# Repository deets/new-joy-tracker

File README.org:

* New Joy Sensor Board

This is documentation for the sensor board I'm developing.

** Sensor Cable Color Coding

I use a 5-wire cable to support the external pressure sensors.

The following table lists the assignment of functions to color:

|--------+----------+---------+--------------|
| Color  | Function | DIN Pin | Sensor Board |
|--------+----------+---------+--------------|
| Black  | GND      |       1 |            1 |
| Brown  | 5V       |       5 |            5 |
| Grey   | 3.3V     |       X |            X |
| Yellow | SDA      |       4 |            4 |
| Blue   | SCL      |       3 |            3 |
|--------+----------+---------+--------------|

** Price Calculation

All calculations are based on a total of 20 Boards.

| Component       | Price per unit |
|-----------------+----------------|
| PCB             |           9.00 |
| ESP32           |          10.00 |
| DC/DC Converter |           4.00 |
|                 |                |

** PCB 

  - https://portal.multi-circuit-boards.eu/
  - [[https://www.amazon.de/gp/product/B0178DX1ZC/ref%3Doh_aui_search_detailpage?ie%3DUTF8&psc%3D1][DC/DC converter]]
  - [[https://www.reichelt.de/OeLFLEX-CLASSIC/CL100-5G0-5-50/3/index.html?ACTION%3D3&LA%3D3&ARTICLE%3D165213&GROUPID%3D7698&trstct%3Dvrt_pdn][5 wire cable]]
  - [[https://e2e.ti.com/support/interface/i2c/f/390/t/615703?P82B715-Not-reading#][P82B715 setup example]]
  - [[http://www.mathertel.de/Arduino/DMXShield.aspx][Good explanation of DMX transmitter setup]]
  - [[https://www.youtube.com/watch?v%3D8NDq6hC9KJo][ESP32 power consumption assessment]]
  - [[https://github.com/clacktronics/pyb_dmx/blob/master/dmx.py][Crappy but useful uPy implementation of DMX]]
  - [[https://de.wikipedia.org/wiki/DMX_(Lichttechnik)][DMX connector assignment]]
  - [[https://www.element14.com/community/groups/open-source-hardware/blog/2017/08/24/dmx-explained-dmx512-and-rs-485-protocol-detail-for-lighting-applications][Nice DMX512 intro]]
  - [[https://www.reichelt.de/PT15-Pihertrimmer-15mm/PT-15-L-10K/3/index.html?ACTION%3D3&LA%3D446&ARTICLE%3D14951&GROUPID%3D3128&artnr%3DPT%2B15-L%2B10K&SEARCH%3Dtrim%252Bpoti%252B10K&trstct%3Dpos_0][Trimm-Poti 10K]]
  - [[https://www.reichelt.de/Elkos-SMD-Low-ESR-105-C/SMD-ELKO-10-35/3/index.html?ACTION%3D3&LA%3D446&ARTICLE%3D31907&GROUPID%3D4001&artnr%3DSMD%2BELKO%2B10%252F35&SEARCH%3Dsmd%252Belko&trstct%3Dpos_1][SMD Elko]]

*** Pull up calculation

According to the P82B715 datasheet we need to calculate the pullups for the buffered bus as follows:

#+BEGIN_QUOTE
R = 1 μs/(C_device + C_wiring)

where

 - C_device = Sum of any connected device capacitances
 - C_wiring = Total wiring and stray capacitance on the bus section 

If these capacitances cannot be measured or calculated, an
approximation can be made by assuming that each device presents 10 pF
of load capacitance and 10 pF of trace capacitance, and that cables
range from 50 pF to 100 pF per meter.
#+END_QUOTE
 
For our use-case with up to 4 devices connected, the calculation should be

4 devices connected with a meter cable each:

20pF * 4 + (100pF * 4) = 500pF -> 0.000001 / (0.000000000500) = 2KOhm

** ESP32

*** Physical

*** Useful links

 - [[http://esp32.net/#Hardware][Overview of boards from espressif themselves]]
 - [[http://playground.arduino.cc/Main/MPU-6050][MPU6050 programming with the Arduino]]
 - [[https://github.com/kriswiner/ESP32/blob/master/MPU9250_MS5637/MPU9250_MS5637_AHRS.ino][ESP32 IMU Sensor Fusion Project]]
 - [[https://www.adafruit.com/product/439][I2C Light (visible/IR) Sensor ]]
 - [[https://github.com/nkolban/esp32-snippets][ESP32 native SDK snippets]]

*** References

bme280 code pilfered from

  https://github.com/catdog2/mpy_bme280_esp8266

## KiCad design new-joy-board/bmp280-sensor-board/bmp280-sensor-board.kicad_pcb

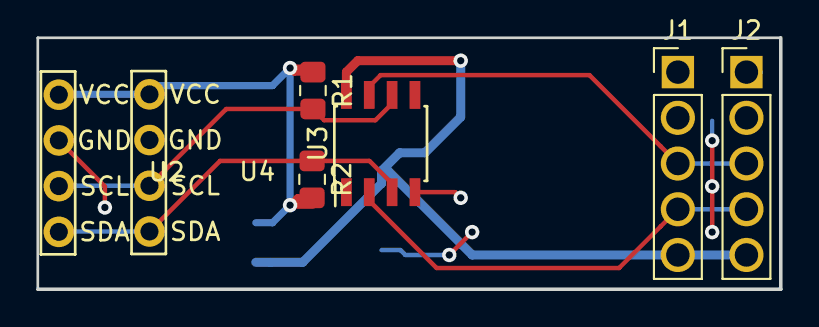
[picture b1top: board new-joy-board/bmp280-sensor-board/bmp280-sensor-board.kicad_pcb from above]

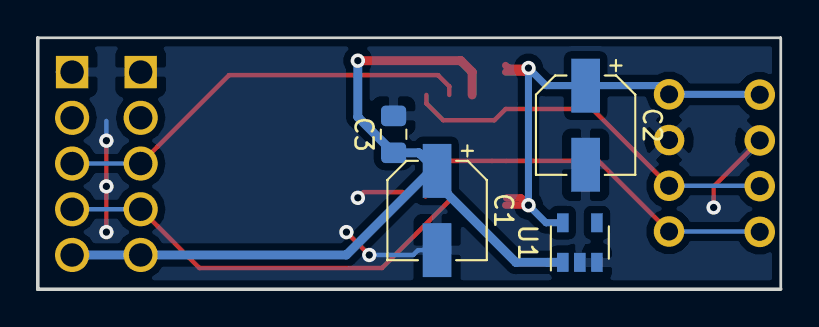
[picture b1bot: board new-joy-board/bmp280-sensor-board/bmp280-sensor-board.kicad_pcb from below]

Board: 2 copper layers, 41.3 x 14.0 mm, 11 parts (4 on the bottom side), 7 nets.

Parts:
C1, C2: 47uF; CP_Elec_5x5.8
C3: 0.1uF; C_0805_2012Metric_Pad1.15x1.40mm_HandSolder
J1, J2: Conn_01x05; Buffered-I2C-Cable-Connector
R1, R2: 2K2; R_0805_2012Metric_Pad1.15x1.40mm_HandSolder
U1: TPS76933; SOT-23-5
U2, U4: generic-i2c-device
U3: P82B715; P82B715D

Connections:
+3V3: C2.1, R1.1, R2.2, U1.5, U2.1, U4.1
+5V: C1.1, C3.1, J1.5, J2.5, U1.1, U3.8
/SCL: R1.2, U2.3, U3.6, U4.3
/SCLBUF: J1.3, J2.3, U3.7
/SDA: R2.1, U2.4, U3.3, U4.4
/SDABUF: J1.4, J2.4, U3.2
GND: C1.2, C2.2, C3.2, J1.1, J2.1, U1.2, U1.3, U2.2, U3.4, U4.2

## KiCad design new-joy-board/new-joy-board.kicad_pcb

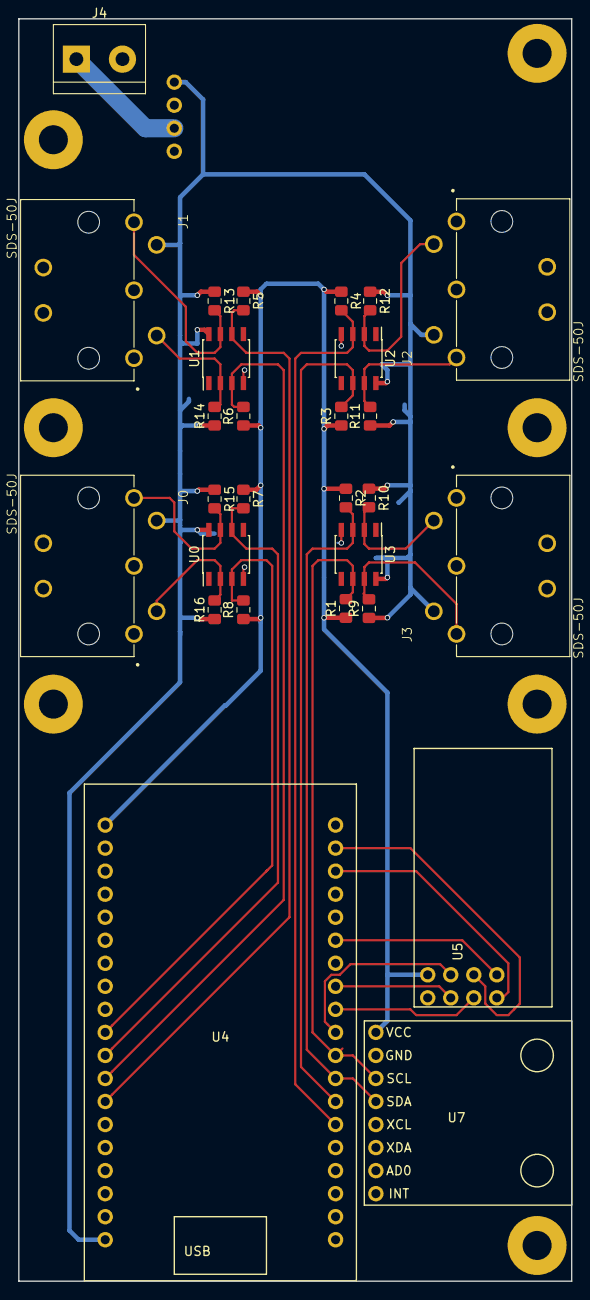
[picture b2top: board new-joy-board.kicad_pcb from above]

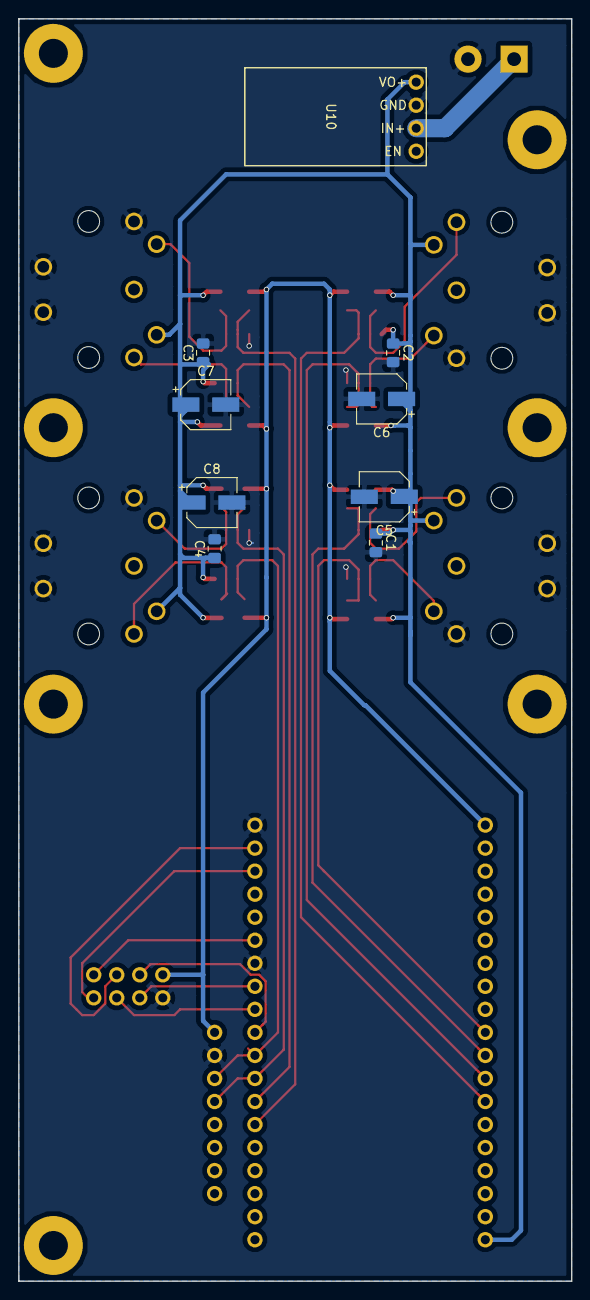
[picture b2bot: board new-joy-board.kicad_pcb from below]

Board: 2 copper layers, 61.0 x 139.2 mm, 37 parts (9 on the bottom side), 26 nets.

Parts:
C1, C2, C3, C4: 0.1uF; C_0805_2012Metric_Pad1.15x1.40mm_HandSolder
C5, C6, C7, C8: 47uF; CP_Elec_5x5.8
J0, J1, J2, J3: SDS-50J; CUI_SDS-50J
J4: BAT; TerminalBlock_bornier-2_P5.08mm
R1, R2, R3, R4, R5, R6, R7, R8, R9, R10, R11, R12, R13, R14, R15, R16: 2K2; R_0805_2012Metric_Pad1.15x1.40mm_HandSolder
U0, U1, U2, U3: P82B715; P82B715D
U4: AZReady_ESP32
U5: 24L01
U7: MPU6050_Breakout
U10: oskj-dc-dc

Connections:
+3V3: R1.1, R2.1, R3.1, R4.1, R5.1, R6.1, R7.1, R8.1, U4.1, U5.8, U7.1
+5V: C1.1, C2.1, C3.1, C4.1, C5.1, C6.1, C7.1, C8.1, J0.5, J1.5, J2.5, J3.5, R9.1, R10.1, R11.1, R12.1, R13.1, R14.1, R15.1, R16.1, U0.8, U1.8, U2.8, U3.8, U4.19, U10.1
+BATT: J4.1, U10.3
-BATT: C1.2, C2.2, C3.2, C4.2, C5.2, C6.2, C7.2, C8.2, J0.1, J0.S1, J0.S2, J1.1, J1.S1, J1.S2, J2.1, J2.S1, J2.S2, J3.1, J3.S1, J3.S2, J4.2, U0.4, U1.4, U2.4, U3.4, U4.32, U4.38, U5.4, U7.2, U10.2
/CE: U4.31, U5.3
/CLK: U4.30, U5.2
/CS0: U4.29, U5.7
/IRQ: U4.33, U5.5
/MISO: U4.36, U5.1
/MOSI: U4.37, U5.6
/SCL0BUF: J0.3, R15.2, U0.7
/SCL0ESP: R7.2, U0.6, U4.11
/SCL1BUF: J1.3, R13.2, U1.7
/SCL1ESP: R5.2, U1.6, U4.13
/SCL2BUF: J2.3, R11.2, U2.7
/SCL2ESP: R3.2, U2.6, U4.26
/SCL3BUF: J3.3, R9.2, U3.7
/SCL3ESP: R1.2, U3.6, U4.28, U7.3
/SDA0BUF: J0.4, R16.2, U0.2
/SDA0ESP: R8.2, U0.3, U4.10
/SDA1BUF: J1.4, R14.2, U1.2
/SDA1ESP: R6.2, U1.3, U4.12
/SDA2BUF: J2.4, R12.2, U2.2
/SDA2ESP: R4.2, U2.3, U4.25
/SDA3BUF: J3.4, R10.2, U3.2
/SDA3ESP: R2.2, U3.3, U4.27, U7.4

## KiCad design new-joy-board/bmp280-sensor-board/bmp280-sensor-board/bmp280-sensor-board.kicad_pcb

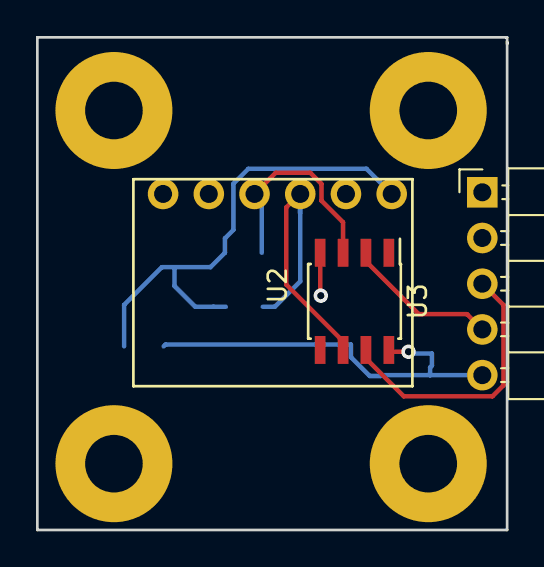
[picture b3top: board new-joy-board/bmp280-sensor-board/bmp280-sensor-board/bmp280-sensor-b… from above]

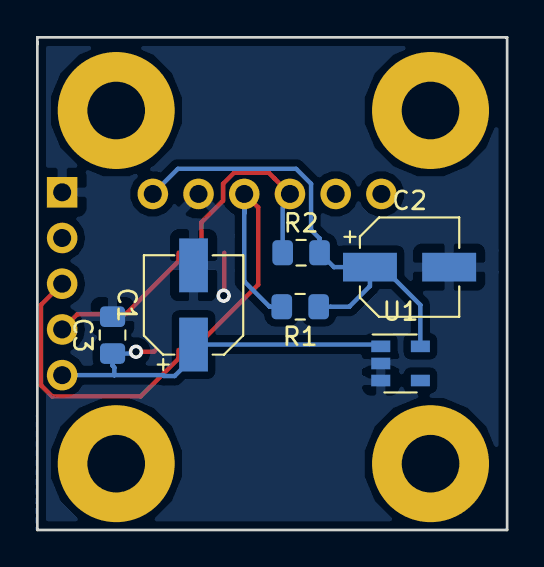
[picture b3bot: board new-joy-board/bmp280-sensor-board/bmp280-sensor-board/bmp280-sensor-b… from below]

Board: 2 copper layers, 26.1 x 27.4 mm, 9 parts (6 on the bottom side), 7 nets.

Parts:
C1, C2: 47uF; CP_Elec_5x5.8
C3: 0.1uF; C_0805_2012Metric_Pad1.15x1.40mm_HandSolder
J1: Conn_01x05; PinHeader_1x05_P2.54mm_Horizontal
R1, R2: 2K2; R_0805_2012Metric_Pad1.15x1.40mm_HandSolder
U1: TPS76933; SOT-23-5
U2: bmp280-board; bmp280-board-footprint
U3: P82B715; P82B715D

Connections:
+3V3: C2.1, R1.1, R2.2, U1.5, U2.1
+5V: C1.1, C3.1, J1.5, U1.1, U3.8
/SCL: R1.2, U2.3, U3.6
/SCLBUF: J1.3, U3.7
/SDA: R2.1, U2.4, U3.3
/SDABUF: J1.4, U3.2
GND: C1.2, C2.2, C3.2, J1.1, U1.2, U1.3, U2.2, U3.4

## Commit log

2018-06-08 First commit, simple setup and readout of bmp280 works
2018-06-15 Begin work on ESP and other component library
2018-06-15 First iteration footprint
2018-06-15 part update
2018-06-15 Began price calculation
2018-06-16 First stab at dc_dc_converter
2018-06-16 silk screen outline
2018-06-16 Associate footprints and adjust pads for library
2018-06-16 3V3 power regulator and i2c0 bus
2018-06-16 Add MPU6050 breakout board schematic and footprint
2018-06-16 Update documentation
2018-06-17 Add Datasheets
2018-06-17 Add P82B715 I2C extender to library
2018-06-17 Updated datasheet
2018-06-17 Add concrete component links and I2C bus impedance calculation
2018-06-17 Worked on design, including DMX and buffered I2C
2018-06-22 Implemented first stab of network setup and broadcasting
2018-06-24 Integrate MPU6050 from https://github.com/larsks/py-mpu6050
2018-06-29 Start working on actual message protocol
2018-06-29 Enhance protocol with timestamp and sequence number
2018-06-29 Control app first version
2018-06-29 Auto-start
2018-06-29 wip: report memory usage
2018-07-29 Setup pipenv
2018-07-29 wip: memory leak
2018-07-29 Upgrade to kicad 5
2018-07-29 Add __main__ section to protocol to monitor without GUI
2018-07-29 Remove superfluous socket option
2018-07-29 Only publish changed sources
2018-07-29 define I2C bus cable coloring
2018-07-29 Add repl script
2018-08-17 Add caching to the publish script to speed things up
2018-08-18 Concept sketch for my PCB I2C bus driver mockup
2018-08-18 Add LDO LMS1587 datasheet
2018-08-18 Rework to use TCP with concrete destination address
2018-08-18 Send IMU data and introduce async server to receive it
2018-08-18 Just a bit of documentation
2018-08-18 Add minimal test program to verify UDP broadcast bug
2018-08-18 Add time.sleep as per suggestion in the forum
    https://forum.micropython.org/viewtopic.php?f=18&t=5063&p=29437&sid=c42123d934024a01ba000141c4625672#p29437
2018-08-18 Add simple helper aliases to source
2018-08-18 Fix bug introduced by hapless rebasing
2018-08-18 Add MIT LICENSE
2018-08-18 Rework network and mainloop code to reconnect to server
2018-08-18 Read both gyro and barometer and send both over with protocol
2018-08-18 Return None if the barometer can't be found at startup
2018-08-18 Add protocol to datagram
    While this is not fool-proof, it seems to improve the
    situation significantly
2018-08-18 Hard reset after reconnection timouts
    This hopefully makes the system even more robust against
    connection losses.
2018-08-20 Add pythonosc to the pipenv
2018-08-20 Send OSC messages
2018-08-20 Adapt to mac
2018-08-20 Allow the ESP RTOS to recover a bit
2018-08-21 Add small visualisation prototype
2018-08-21 Integrate visualisation with async server
2018-08-21 Refactor server into package
2018-08-21 Split out package parsing
2018-08-21 Installed nose and pylint
2018-08-21 Send gyro x, and visualise it
2018-08-21 Send all IMU data
2018-08-22 Add AtomExplosion credentials configured for CPE
2018-08-22 A bit robustness for setting up the wifi
2018-08-22 Interesting link for IMU procssing with the ESP32
2018-08-22 Add packet time diff for statistics gathering
2018-08-22 Interesting link for a light sensor
2018-08-22 Use UDP as it's MUCH more responsive
2018-08-24 Add cargo-cult-code-line in hopes of soothing the gods of ESP
2018-08-25 Add DIN connector with 3d representation
2018-08-25 Replace 3d model with existing one
2018-08-25 Add footprint for 3mm drill-hole to mount pcb
2018-08-25 Work on schematic and PCB to mock up real PCB
2018-08-26 Use UDP protocol to resolve IPs to MACs for further use
2018-08-26 More PCB work to determine final dimensions for case construction
2018-08-31 Add simple native application as starting point
2018-09-02 Migrated to app-format so that 3d visualisation can work
2018-09-02 Adapted server and visualisation to send name
2018-09-02 Determine 4 pin-combinations for I2C interfaces
2018-09-02 Interesting ESP32 link added to docs
2018-09-02 Reworked id system as macs aren't working
2018-09-02 Some fine-tuning on the display
2018-09-07 Add name resolving via unique id mapping
2018-09-07 Use name in visualisation
2018-09-07 Registered the first 9 or so names
2018-09-07 Allow MPU to be not connected for testing purposes
2018-09-07 Wired up 3 more boards and assigned names
2018-09-07 Output of individual values only on debug level
2018-09-09 Add new DC/DC module that we use
2018-09-09 Routet half of the I2C buffers
2018-09-09 First draft of full layout
2018-09-14 Add wifi module with text-based config
2018-09-14 Start rework to slimmer design, and add capacitors to I2C drivers
2018-09-14 ignore my invoices - the world doesn't need to see them ;)
2018-09-14 Use explicit path
2018-09-14 NOP logging callback
2018-09-14 Add SQLite based logging of packages
2018-09-14 Reworked to sendto to allow for broadcasting
2018-09-14 Add NRF24 board to library
2018-09-14 Route new board layout
2018-09-16 Designed in the 24L01 board for emergency use
2018-09-16 Replaced the 1uF with 47uF Elekos as per David's recommendation
2018-09-21 Generated manufacturing files and ordered PCB
2018-09-21 The current revision of the 3D-printed case
2018-09-21 Roll-over reduced as otherwise my notebook can't deal with the many graphs
2018-09-22 Added the missing solder mask layers
2018-09-22 Add bokeh-based analyse script for my latency test
2018-09-22 Ignore artifact
2018-10-03 Add better command line argument help
2018-10-03 Improve publish script to take src/<fname> and always force-push.
2018-10-03 CARL is here!
2018-10-03 Choose right I2C bus pins for the mockup
2018-10-03 Added some instructions
2018-10-03 Datasheets for pressure sensor and LDO
2018-10-03 New version of base board pcb with bigger holes
2018-10-03 Add BMP280 breakout board to schema and footprint libs
2018-10-03 Properly laid out the MPU library
2018-10-03 Added mounting-holes
2018-10-03 New version of case with bigger screw holes
2018-10-03 Fix pads for through-the-hole boards
2018-10-03 Add MPU datasheet
2018-10-03 Use newjoy module to drive sensors
2018-10-03 Exchanged new footprints with bigger pads in the boards
2018-10-03 Placed MPU6050 as additional option
2018-10-03 Removed superfluous subdirectory
2018-10-03 Add labels to bmp footprint
2018-10-03 Add generic I2C device footprint
2018-10-19 Continue work on daughter board
2018-10-20 Correct I2C port setup
2018-10-20 Add DIN pin mapping to cable description
2018-10-20 Prolonged daughter board and added footprint for better soldering
2018-10-20 wip: removed unused files for testing
2018-10-20 Better manufacturing file scripts
2018-10-20 Resized board to conform with multi cb
2018-11-16 Sensor Board cable documentation
2018-11-17 Simplify setup
2018-11-17 wip: hack printing of BMP280 values
2018-11-17 wip: no mpu setup
2018-11-17 wip: scan for mpu
2018-11-17 Properly register bmp280 and MPU
2018-11-17 Remove outdated info
2018-11-17 Parse descriptor correctly and create full data
2018-11-18 MPU6050 also communicates acc data now
2018-11-18 Directly send OSC messages from the devices
2018-11-24 Fix publish.sh that got broken in the uosc reworking
2018-11-24 Add OSC descriptor
2018-11-24 Better OSC setup
2018-11-24 Only send OSC
2018-12-08 Deal with apparent MPU6050 variances in identification
2018-12-08 Remove superflous and confusing print statement
2018-12-15 Add latest firmware and meanst to flash using esptool
2018-12-19 Little helper function for cleaning up the filesystem
2018-12-19 Make flash script take the port as argument
2018-12-19 Added test-programs for nrf24l01
    The system works. Wooooot!
    Taken from https://github.com/micropython/micropython/tree/master/drivers/nrf24l01
2019-01-01 Removed assertion for BMP280 as it sometimes seems to answer differently ?!?
2019-01-01 Add datasheet
2019-01-01 Use name as OSC path
2019-01-01 Take port as argument
2019-01-01 Initial NRF24 communication going
2019-01-01 Tweaked retries and speeds
2019-01-04 Removed superfluous arpreq
2019-01-12 Add 3D-models
2019-01-12 Implement spoke/hub-protocol in C
2019-01-12 Use NRF24 to send protocol data
2019-01-12 Give name to latest ESP32 - TIMO, who will become the head station
2019-01-12 Publishing and repling with higher speed
2019-01-13 Began working on hub relay
2019-01-13 More work on hub-relay, base message parser
2019-01-13 Fix waiting code
2019-01-18 latest firmware
2019-01-18 Activated SINA
2019-01-18 Renamed BOOT button toggle from RAW to DEBUG making it clearer
2019-01-18 Adapted visualisation to hub based protocol
2019-01-18 Split up into several osc packages with running number prefix
2019-01-18 Remove BMP sensors as we don't use them right now
2019-01-19 Add sleep to debug mode send rate
2019-01-19 Use OTTO as hub, IRIS as spoke
2019-01-19 Fix test for new protocol with descriptor and packet diff
2019-01-19 Add type flag to protocol
    This took WAY too long
2019-01-19 Move hub-relay into its own package
2019-01-19 Introduce hub status messages
2019-01-19 Some better debugging output
2019-01-19 Use select to wait for incoming data
2019-01-19 Remove print
2019-01-19 Use UART2 for communication
2019-01-19 Increase statistics output and prevent some crashing
2019-01-19 Use uart2 directly
2019-01-20 Initial port of SPP acceptor into NJ
2019-01-20 Converted to C++
2019-01-20 Add initiator from SDK
2019-01-20 Renamed
2019-01-20 Rework spoke to send faked sensor package
2019-01-21 Latest firmware with 115200 Baud, more logging after startup
2019-01-21 Add debug-pin functionality
2019-01-21 Fix osc offset bug
2019-01-22 Make joining network chosable, debugpin prints task-info
2019-01-22 Debug-pin is not on by default, newjoy.max_task_time added
2019-01-22 Enhance debug-pin behaviour, but turn it off by default
2019-01-22 moving average firmware, 5 seconds leadin
2019-01-23 Remove NRF24 cruft
2019-01-23 Add RALF
2019-01-24 Add uptime timestamp as first argument to OSC message
2019-01-24 Add initial version of the quaternion investigator
2019-01-24 Cleaned up qrep
2019-01-24 Move qrep into own class and translated into middle before applying rotation
2019-01-24 Use actual quaternion to rotate
2019-01-24 Add plot-widget in second window, save/restore window state
2019-01-24 Update plot by angles to show-case this updating
2019-01-24 Add source to angle plot to select the two quats the angle is being computed between
2019-01-26 dropme: direct connect to first network. This does not really work!
2019-01-26 Add basic OSC receiving functionality
2019-01-26 Hook actual quaternions from OSC into the reps
2019-01-26 Use choice of selection to compute angle between quats
2019-02-01 Remove old an unused angelia code
2019-02-01 Moved QI into own submodule
2019-02-01 Try and make the app quittable even if it's not fed OSC
2019-02-01 Replaced cylinder with coordinate root
2019-02-01 Work on file-based OSC data acquisition
2019-02-01 Using rxpy to process some quaternions. neat.
2019-02-02 Emit signal with subsequent angle
2019-02-02 Start working on better layout and path-based plots
2019-02-02 Name the gizmos with board/sensor-no
2019-02-02 Set up windows for paths, including restoring their state
2019-02-02 Restore angle plot source selection and display
2019-02-02 We have a working reset button
2019-02-02 Listen to incoming messages, and process R for reset
2019-02-02 Implement masking of sensor sending, and more robust connection code
2019-02-02 Add MaskController
2019-02-02 ignore /IGNORE. As god intended
2019-02-08 Account for changed ACC handling
2019-02-08 Implement updating the gain
2019-02-08 Introduce ACC display
2019-02-08 Restore default behaviour
